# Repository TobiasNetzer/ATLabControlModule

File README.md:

# ATLab - Control Module

A two‑button control interface that mounts directly to the test fixture using interchangeable custom backplates.
It provides a simple start/stop input for executing test jobs.

While the LED status bar indicates the current test state:
- Idle
- Pass
- Fail
- Running
- Cancelled

Each button also has individually adjustable backlighting that can signal when operator action is required.

**Docs:**  
- [Schematic](docs/ATLabControlModule%20-%20Schematic.pdf)
- [Assembly Drawing](docs/ATLabControlModule%20-%20Assembly%20Drawing.pdf)

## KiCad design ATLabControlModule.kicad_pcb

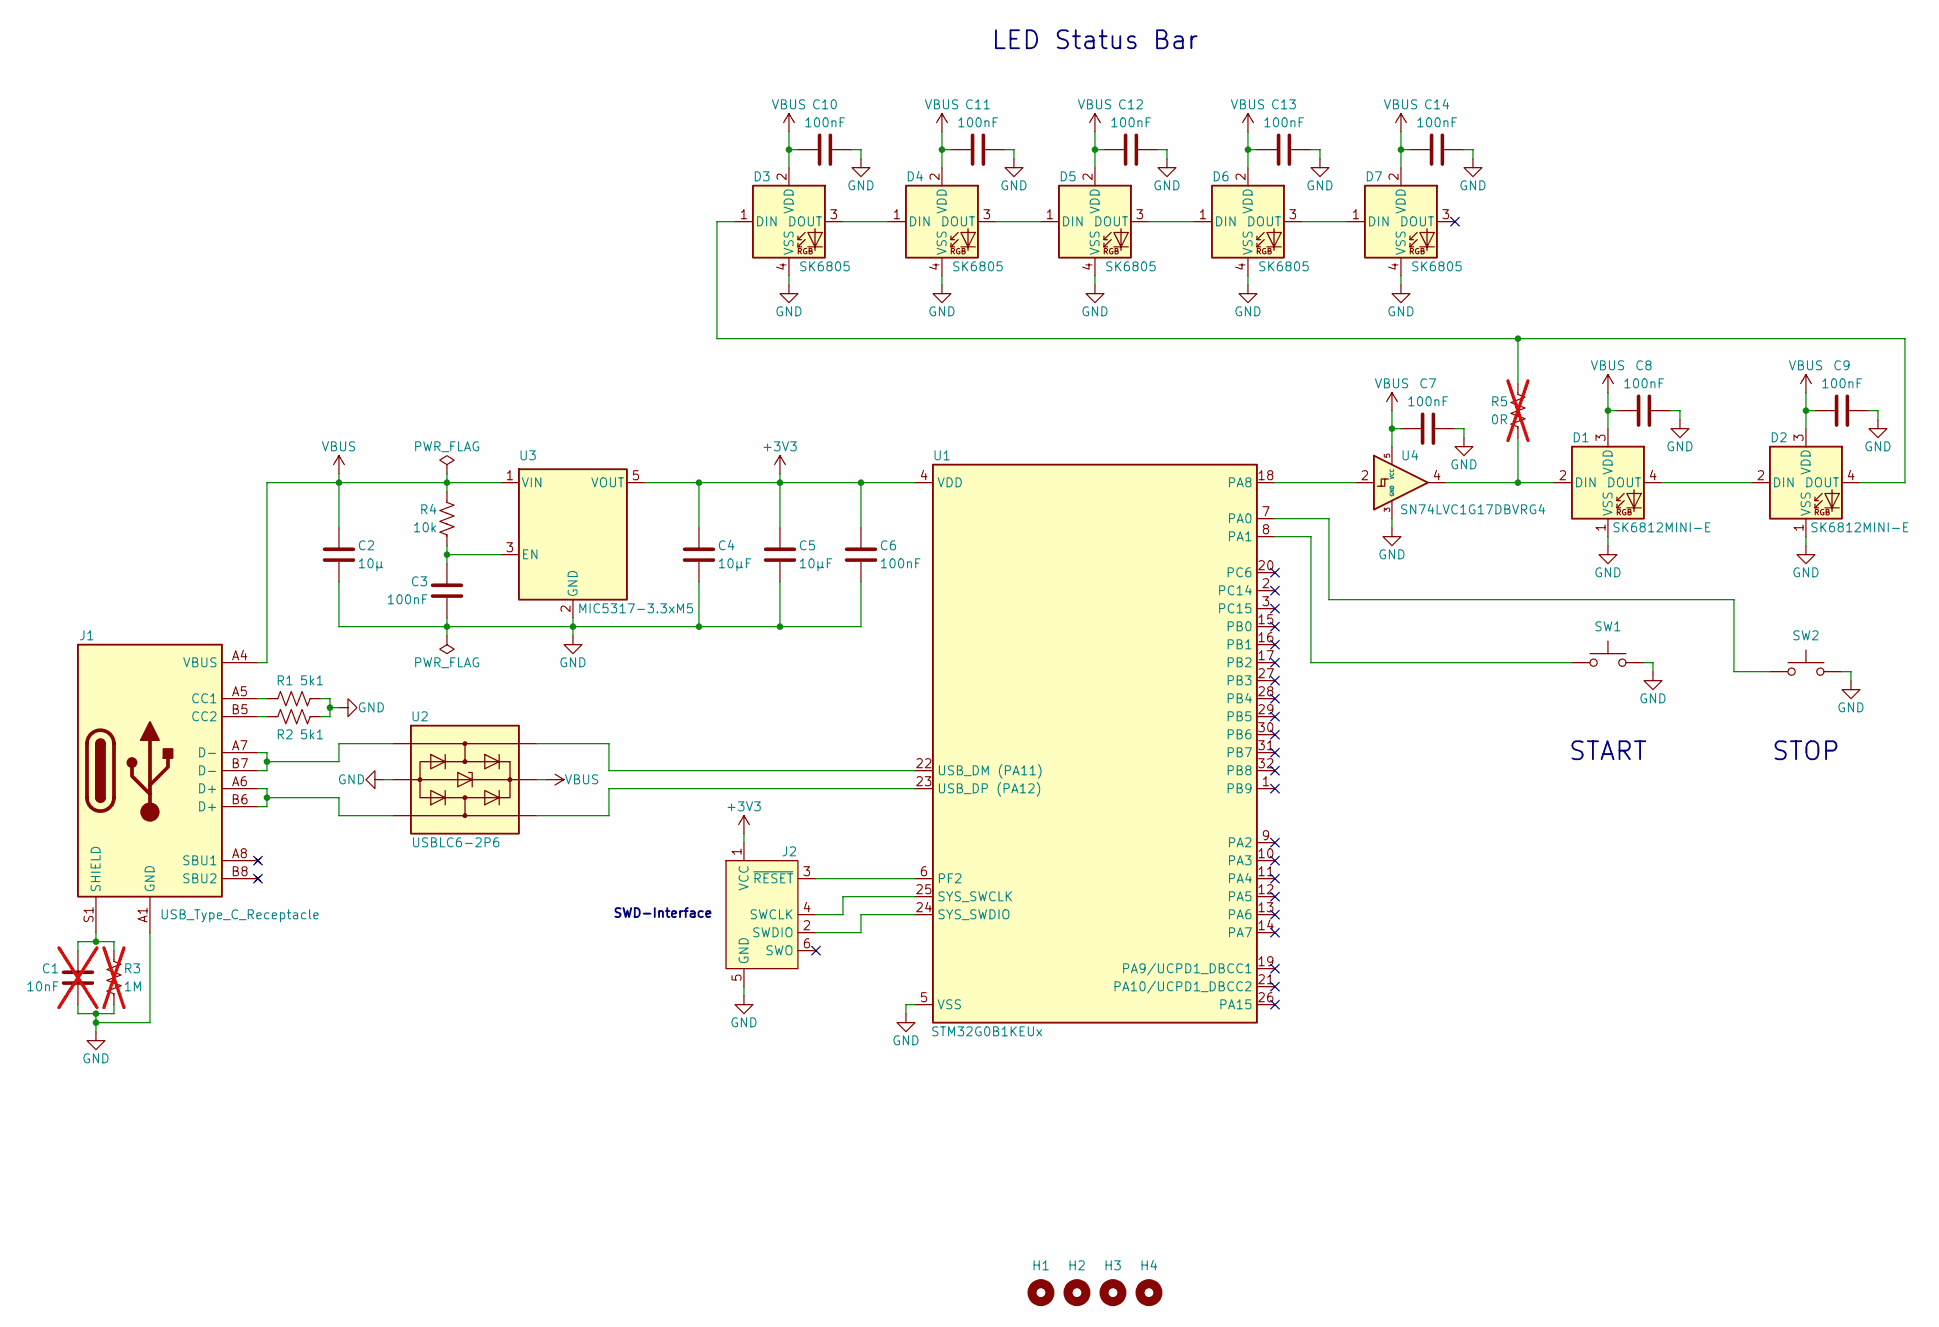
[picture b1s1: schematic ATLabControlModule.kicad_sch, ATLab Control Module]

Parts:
C1: 10nF; C_1206_(3216_Metric); not fitted
C2: 10µ; C_0805_(2012_Metric)
C3, C6, C7, C8, C9, C10, C11, C12, C13, C14: 100nF; C_0402_(1005_Metric)
C4, C5: 10µF; C_0805_(2012_Metric)
D1, D2: SK6812MINI-E; LED_SK6812MINI-E_3.2x2.8mm_P1.5mm_ReverseMount; Manufacturer Part Number SK6812MINI-E
D3, D4, D5, D6, D7: SK6805; LED_SK6812_EC15_1.5x1.5mm; Manufacturer Part Number SK6805-EC15
H1, H2, H3, H4: MountingHole; Mounting_Hole
J1: USB_Type_C_Receptacle; USB_C_Receptacle_HRO_TYPE-C-31-M-12; Manufacturer Part Number USB_C_Receptacle_HRO_TYPE-C-31-M-12
J2: Conn_ARM_SWD_TagConnect_TC2030; Tag-Connect_TC2030-IDC-NL_2x03_P1.27mm_Vertical
R1, R2: 5k1; R_0402_(1005_Metric)
R3: 1M; R_1206_(3216_Metric); not fitted
R4: 10k; R_0402_(1005_Metric)
R5: 0R; R_0402_(1005_Metric); not fitted
SW1, SW2: Kailh_Choc_V2_Brown; SW_Kailh_Choc_V2; Manufacturer Part Number CPG135301D02
U1: STM32G0B1KEUx; QFN-32-1EP_5x5mm_P0.5mm_EP3.45x3.45mm; Manufacturer Part Number STM32G0B1KEU6
U2: USBLC6-2P6; SOT-666; Manufacturer Part Number USBLC6-2P6
U3: MIC5317-3.3xM5; SOT-23-5; Manufacturer Part Number MIC5317-3.3YM5-TR
U4: SN74LVC1G17DBVRG4; SOT-23-5; Manufacturer Part Number SN74LVC1G17DBVRG4

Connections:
+3V3: C4.1, C5.1, C6.1, J2.1 (VCC), U1.4 (VDD), U3.5 (VOUT)
GND: C1.2, C2.2, C3.2, C4.2, C5.2, C6.2, C7.2, C8.2, C9.2, C10.2, C11.2, C12.2, C13.2, C14.2, D1.1 (VSS), D2.1 (VSS), D3.4 (VSS), D4.4 (VSS), D5.4 (VSS), D6.4 (VSS), D7.4 (VSS), J1.A1 (GND), J1.A12 (GND), J1.B1 (GND), J1.B12 (GND), J2.5 (GND), R1.2, R2.2, R3.2, SW1.2, SW2.2, U1.5 (VSS), U1.33 (VSS), U2.2 (GND), U3.2 (GND), U4.3 (GND)
unnamed: D1.2 (DIN), R5.2, U4.4
unnamed: D1.4 (DOUT), D2.2 (DIN)
unnamed: D2.4 (DOUT), D3.1 (DIN), R5.1
unnamed: D3.3 (DOUT), D4.1 (DIN)
unnamed: D4.3 (DOUT), D5.1 (DIN)
unnamed: D5.3 (DOUT), D6.1 (DIN)
unnamed: D6.3 (DOUT), D7.1 (DIN)
unnamed: J1.A5 (CC1), R1.1
unnamed: J1.B5 (CC2), R2.1
unnamed: J1.A6 (D+), J1.B6 (D+), U2.3 (I/O2)
unnamed: J1.A7 (D-), J1.B7 (D-), U2.1 (I/O1)
unnamed: C1.1, J1.S1 (SHIELD), R3.1
unnamed: J2.4 (SWCLK), U1.25 (SYS_SWCLK)
unnamed: J2.2 (SWDIO), U1.24 (SYS_SWDIO)
unnamed: J2.3 (~RESET), U1.6 (PF2)
unnamed: SW2.1, U1.7 (PA0)
unnamed: SW1.1, U1.8 (PA1)
unnamed: U1.18 (PA8), U4.2
unnamed: U1.22 (USB_DM (PA11)), U2.6 (I/O1)
unnamed: U1.23 (USB_DP (PA12)), U2.4 (I/O2)
unnamed: C3.1, R4.2, U3.3 (EN)
VBUS: C2.1, C7.1, C8.1, C9.1, C10.1, C11.1, C12.1, C13.1, C14.1, D1.3 (VDD), D2.3 (VDD), D3.2 (VDD), D4.2 (VDD), D5.2 (VDD), D6.2 (VDD), D7.2 (VDD), J1.A4 (VBUS), J1.A9 (VBUS), J1.B4 (VBUS), J1.B9 (VBUS), R4.1, U2.5 (VBUS), U3.1 (VIN), U4.5 (VCC)

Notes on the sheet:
START
STOP
SWD-Interface
LED Status Bar

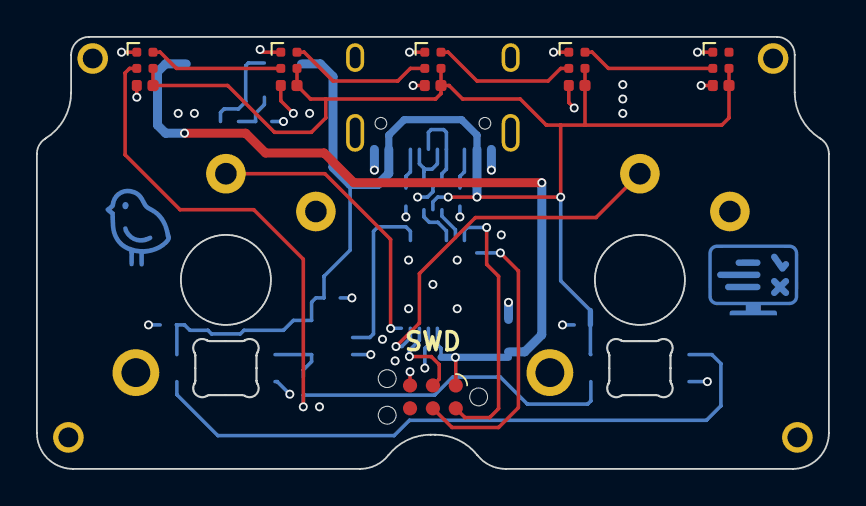
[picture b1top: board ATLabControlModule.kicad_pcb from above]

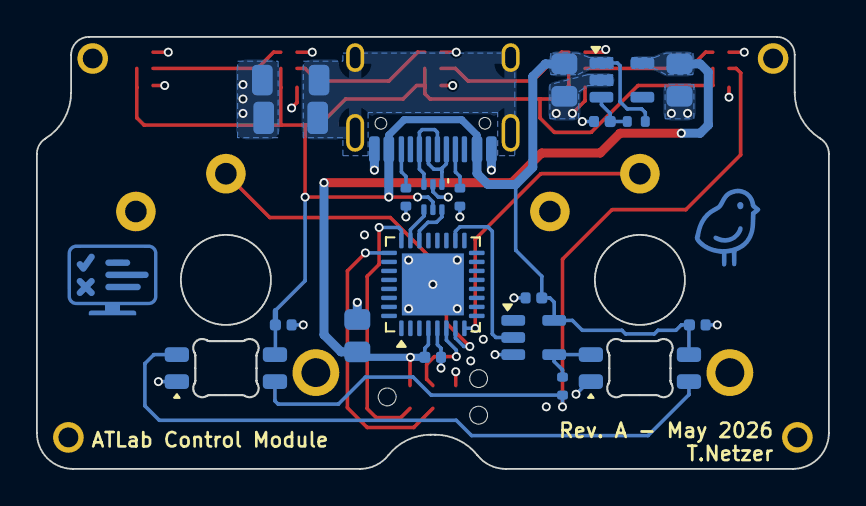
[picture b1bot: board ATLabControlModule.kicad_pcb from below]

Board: 4 copper layers, 44.0 x 24.0 mm, 38 parts (21 on the bottom side), 24 nets.

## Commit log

2026-05-17 Imported symbols and footprints to local library
2026-05-18 update library and schematic
2026-05-19 schematic rev A
2026-05-24 PCB Rev A
2026-05-25 cleanup and add docs
2026-05-25 Add README
2026-05-25 update renders
